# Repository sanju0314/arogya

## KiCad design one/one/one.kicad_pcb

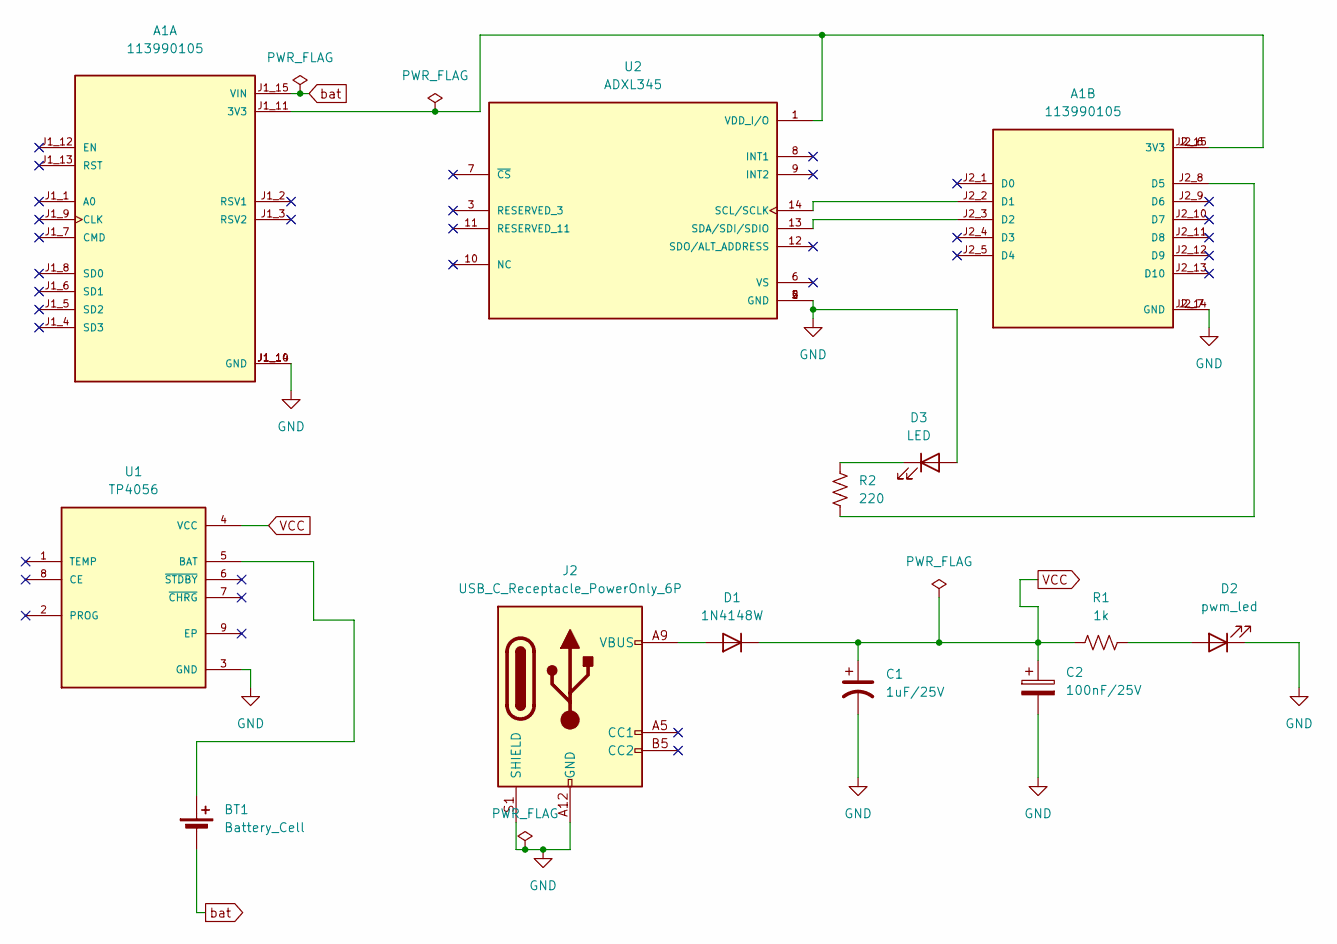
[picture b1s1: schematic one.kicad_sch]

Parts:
A1: 113990105; SEEED_113990105; PARTREV N/A
BT1: Battery_Cell; BatteryHolder_Seiko_MS621F
C1: 1uF/25V; C_0603_1608Metric_Pad1.08x0.95mm_HandSolder
C2: 100nF/25V; C_0603_1608Metric_Pad1.08x0.95mm_HandSolder
D1: 1N4148W; D_SOD-123
D2: pwm_led; LED_0603_1608Metric_Pad1.05x0.95mm_HandSolder
D3: LED; LED_0603_1608Metric_Pad1.05x0.95mm_HandSolder
J2: USB_C_Receptacle_PowerOnly_6P; USB_C_Receptacle_Amphenol_12401548E4-2A
R1: 1k; R_0603_1608Metric_Pad0.98x0.95mm_HandSolder
R2: 220; R_0603_1608Metric_Pad0.98x0.95mm_HandSolder
U1: TP4056; SOP127P600X175-9N
U2: ADXL345; PQFN80P500X300X100-14N; PARTREV B

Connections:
GND: A1.J1_10 (GND), A1.J1_14 (GND), A1.J2_7 (GND), A1.J2_14 (GND), C1.2, C2.2, D2.1 (K), D3.2 (A), J2.A12 (GND), J2.B12 (GND), J2.S1 (SHIELD), U1.3 (GND), U2.2 (GND), U2.4 (GND), U2.5 (GND)
unnamed: A1.J1_11 (3V3), A1.J2_6 (3V3), A1.J2_15 (3V3), U2.1 (VDD_I/O)
unnamed: A1.J2_2 (D1), U2.14 (SCL/SCLK)
unnamed: A1.J2_3 (D2), U2.13 (SDA/SDI/SDIO)
unnamed: A1.J2_8 (D5), R2.2
unnamed: BT1.1 (+), U1.5 (BAT)
unnamed: D1.2 (A), J2.A9 (VBUS), J2.B9 (VBUS)
unnamed: D2.2 (A), R1.2
unnamed: D3.1 (K), R2.1
VCC: C1.1, C2.1, D1.1 (K), R1.1, U1.4 (VCC)
bat: A1.J1_15 (VIN), BT1.2 (-)

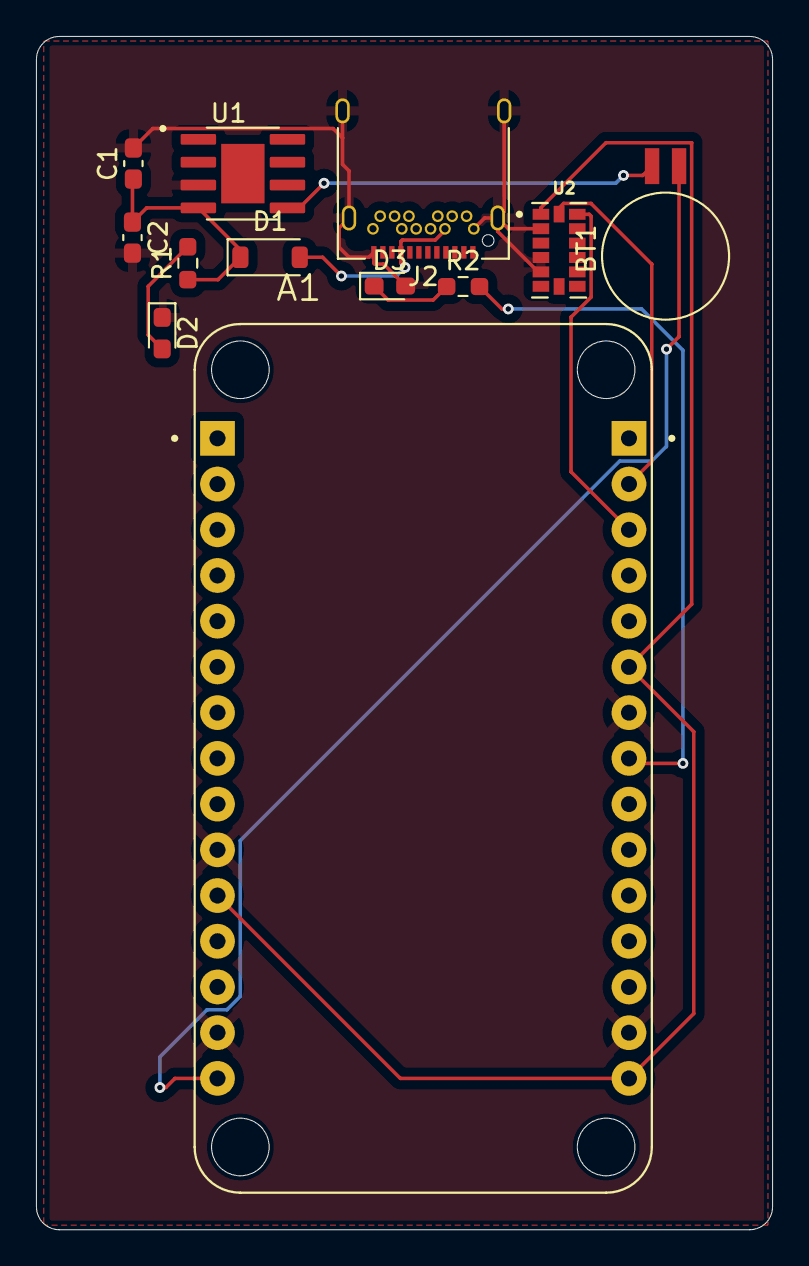
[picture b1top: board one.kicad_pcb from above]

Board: 2 copper layers, 40.9 x 66.3 mm, 12 parts (0 on the bottom side), 11 nets.
